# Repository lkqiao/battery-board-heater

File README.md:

# battery-board-heater
Subproject as part of the Stanford Student Space Initiative (SSI). This project provides the heater circuit used for the battery board of SAMWISE, the 2U CubeSat we are currently working on, to maintain optimal temperature for efficient auxiliary power supply to deployable structures, ADCS, radio, and a 12MP camera + selfie stick. 

The schematic of the heater circuit is provided in KiCAD and is integrated into the main battery board PCB and external systems of the satellite. The coordinates of the heating coil traces are automatically generated via Python script.

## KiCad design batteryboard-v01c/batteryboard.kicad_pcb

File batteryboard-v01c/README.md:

# PyCubed Battery Board

2S3P Li-ion battery pack for CubeSat designs.
   - Fits 18650 cells (like the LG INR18650-MJ1)
   - Meets maximum capacity requirements of common CubeSat integrators
   - Uses components with radiation testing heritage
      - R5460x2xx for protection against
         - over-charge 
         - over-discharge
         - short-circuit
         - excess discharge-current
         - excess charge-current

## Interactive Bill of Materials 🛒
- [batteryboard-v01](https://pycubed.github.io/hardware/batteryboard-v01)

<br>
<br>
<br>
<br />This work is licensed under a <a rel="license" href="http://creativecommons.org/licenses/by/4.0/">Creative Commons Attribution 4.0 International License</a>.

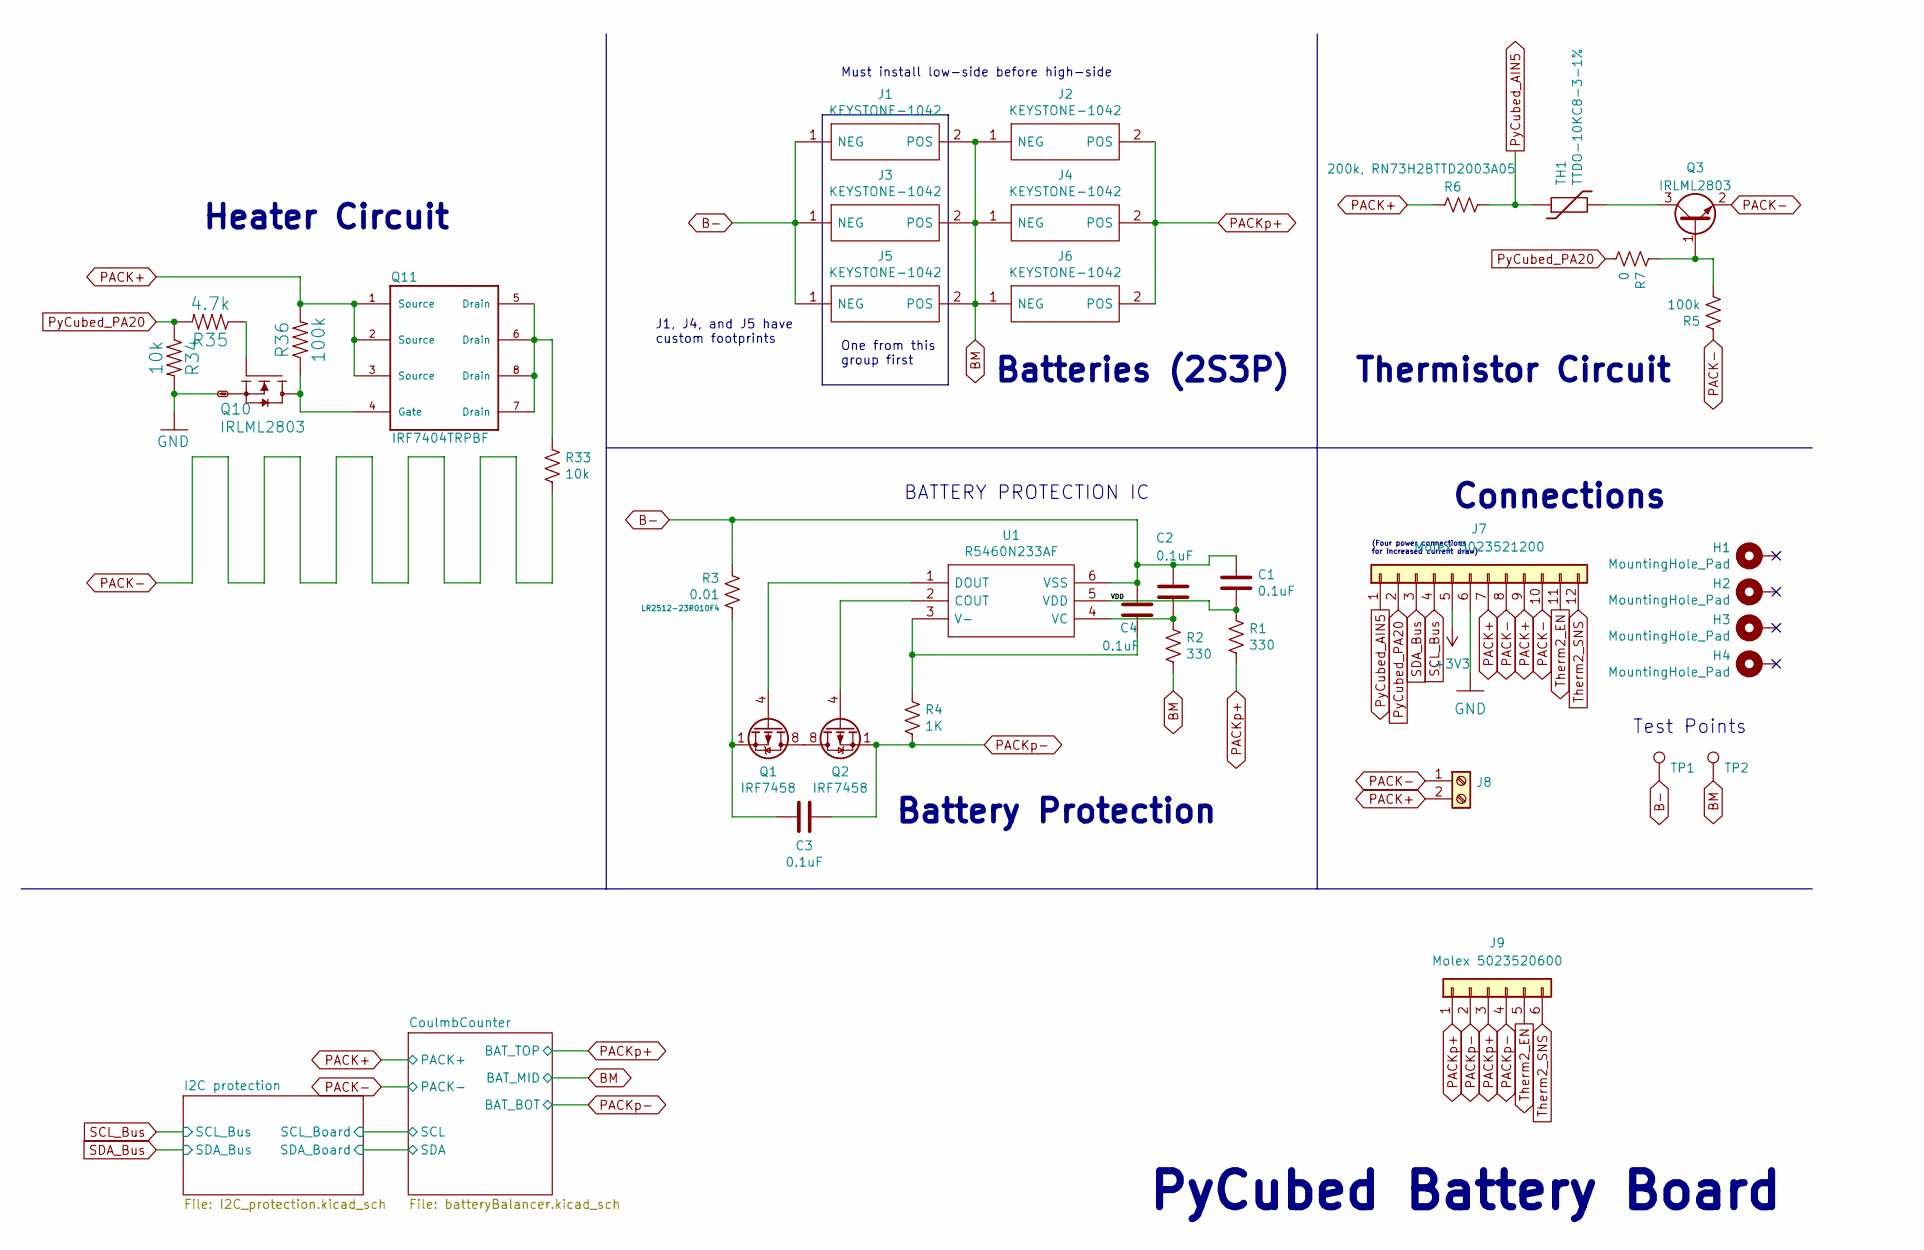
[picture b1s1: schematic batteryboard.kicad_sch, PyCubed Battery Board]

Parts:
C1, C2, C3, C4: 0.1uF; C_0603_1608Metric
H1, H2, H3, H4: MountingHole_Pad; MountingHole_3.2mm_M3_DIN965_PadMOD
J1: KEYSTONE-1042; Keystone_1042_J1; Manufacturer_Part_Number 1042; Mouser Part Number 534-1042
J2, J3, J6: KEYSTONE-1042; Keystone_1042; Manufacturer_Part_Number 1042; Mouser Part Number 534-1042
J4: KEYSTONE-1042; Keystone_1042_J4; Manufacturer_Part_Number 1042; Mouser Part Number 534-1042
J5: KEYSTONE-1042; Keystone_1042_J5; Manufacturer_Part_Number 1042; Mouser Part Number 534-1042
J7: Molex 5023521200; 5023521200
J8: Screw_Terminal_01x02; pheonix_2pos_screwterminal
J9: Molex 5023520600; 5023520600
Q1, Q2: IRF7458; SOIC-8_3.9x4.9mm_P1.27mm
Q3: IRLML2803; SOT-23
Q10: IRLML2803; SOT-23; Manufacturer_Part_Number MMBT2222AT
Q11: IRF7404TRPBF; Manufacturer_Part_Number NDS8434
R1, R2: 330; R_0603_1608Metric
R3: 0.01; R_2512_6332Metric
R4: 1K; R_0603_1608Metric; Manufacturer_Part_Number LR2512-23R010F4
R5, R36: 100k; R_0603_1608Metric
R6: 200k, RN73H2BTTD2003A05; R_1206_3216Metric
R7: 0; R_0603_1608Metric
R33, R34: 10k; R_0603_1608Metric
R35: 4.7k; R_0603_1608Metric
TH1: TTDO-10KC8-3-1%; R_Axial_DIN0204_L3.6mm_D1.6mm_P5.08mm_Horizontal
TP1, TP2: TestPoint; TestPoint_Loop_D1.80mm_Drill1.0mm_Beaded
U1: R5460N233AF; SOT-23-6; Manufacturer_Part_Number R5460N233AF-TR-FE; Mouser Part Number 848-R5460N233AFTRFE

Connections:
+3V3: J7.5; also elsewhere on the board
/VDD: C1.2, R1.2, U1.5 (VDD)
B-: C1.1, C2.1, C4.1, J1.1 (NEG), J3.1 (NEG), J5.1 (NEG), R3.1, TP1.1, U1.6 (VSS)
BM: J1.2 (POS), J2.1 (NEG), J3.2 (POS), J4.1 (NEG), J5.2 (POS), J6.1 (NEG), R2.1, TP2.1; also elsewhere on the board
GND: J7.6, Q10.2 (S), R34.2; also elsewhere on the board
unnamed: C3.1, Q1.1 (S), Q1.2 (S), Q1.3 (S), R3.2
unnamed: Q1.5 (D), Q1.6 (D), Q1.7 (D), Q1.8 (D), Q2.5 (D), Q2.6 (D), Q2.7 (D), Q2.8 (D)
unnamed: Q1.4 (G), U1.1 (DOUT)
unnamed: Q2.4 (G), U1.2 (COUT)
unnamed: Q3.1 (B), R5.1, R7.2
unnamed: Q3.3 (C), TH1.2
unnamed: Q10.3 (D), Q11.4 (Gate), R36.1
unnamed: Q10.1 (G), R35.1
unnamed: Q11.5 (Drain), Q11.6 (Drain), Q11.7 (Drain), Q11.8 (Drain), R33.2
unnamed: C4.2, R4.1, U1.3 (V-)
unnamed: C2.2, R2.2, U1.4 (VC)
PACK+: J7.7, J7.9, J8.2, Q11.1 (Source), Q11.2 (Source), Q11.3 (Source), R6.1, R36.2; also elsewhere on the board
PACK-: J7.8, J7.10, J8.1, Q3.2 (E), R5.2, R33.1; also elsewhere on the board
PACKp+: J2.2 (POS), J4.2 (POS), J6.2 (POS), J9.1, J9.3, R1.1; also elsewhere on the board
PACKp-: C3.2, J9.2, J9.4, Q2.1 (S), Q2.2 (S), Q2.3 (S), R4.2; also elsewhere on the board
PyCubed_AIN5: J7.1, R6.2, TH1.1
PyCubed_PA20: J7.2, R7.1, R34.1, R35.2
SCL_Bus: J7.4; also elsewhere on the board
SDA_Bus: J7.3; also elsewhere on the board
Therm2_EN: J7.11, J9.5
Therm2_SNS: J7.12, J9.6

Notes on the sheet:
Connections
(Four power connections for increased current draw)
One from this group first
PyCubed Battery Board
Batteries (2S3P)
Heater Circuit
Test Points
J1, J4, and J5 have custom footprints
Battery Protection
Must install low-side before high-side
Thermistor Circuit
BATTERY PROTECTION IC

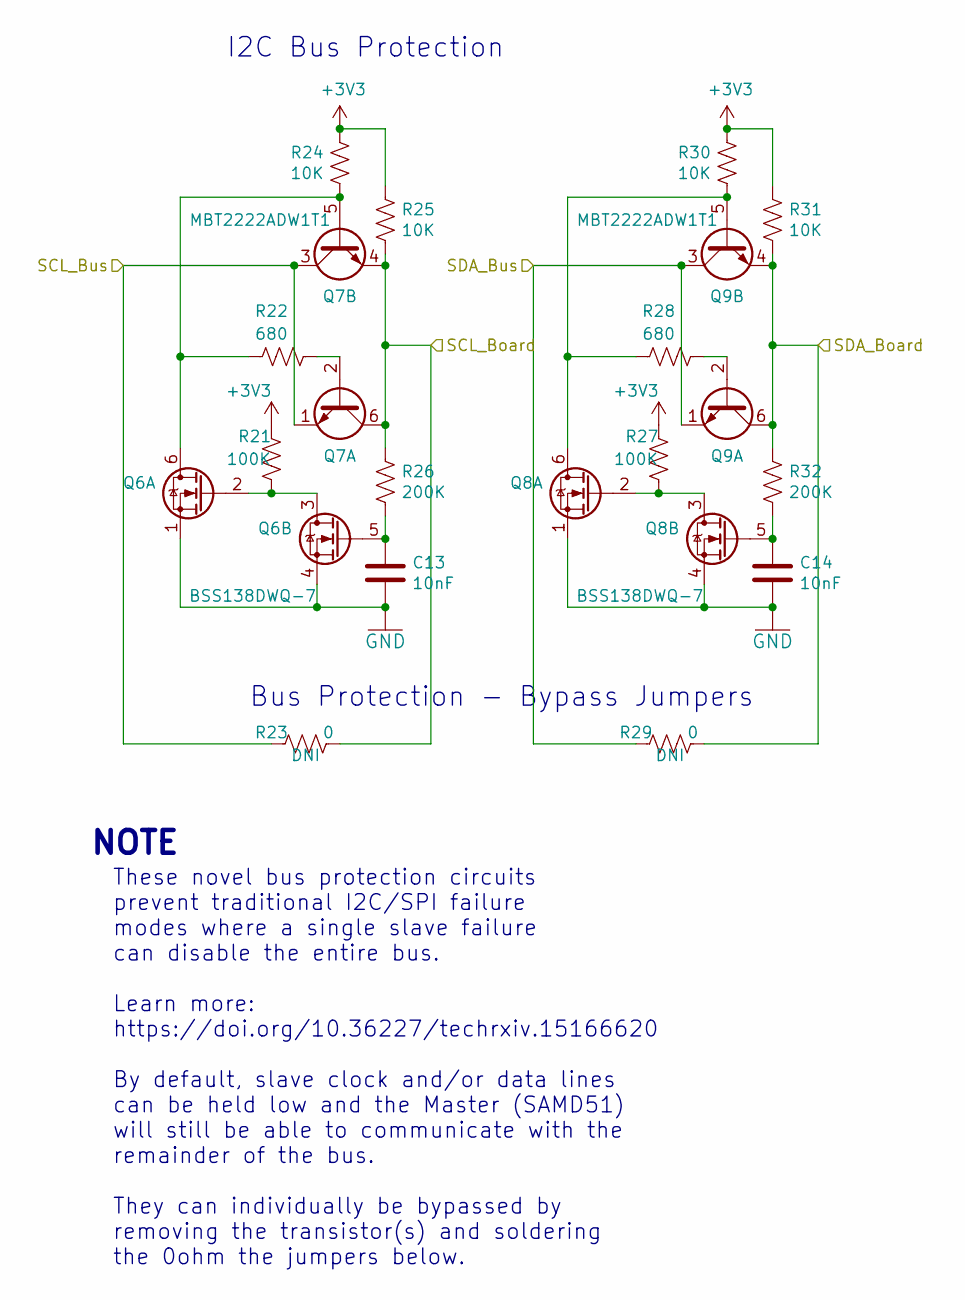
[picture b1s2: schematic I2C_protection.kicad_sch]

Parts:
C13, C14: 10nF; C_0603_1608Metric
Q6, Q8: BSS138DWQ-7; Manufacturer_Part_Number BSS138DWQ-7; Mouser Part Number 621-BSS138DWQ-7
Q7, Q9: MBT2222ADW1T1; SOT-363_SC-70-6; Manufacturer_Part_Number MBT2222ADW1T1G
R21, R27: 100K; R_0603_1608Metric
R22, R28: 680; R_0603_1608Metric
R23, R29: 0; R_0603_1608Metric
R24, R25, R30, R31: 10K; R_0603_1608Metric
R26, R32: 200K; R_0603_1608Metric

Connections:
+3V3: R21.1, R24.1, R25.1, R27.1, R30.1, R31.1; also elsewhere on the board
/CoulmbCounter/SCL: Q7.4 (E2), Q7.6 (C1), R23.1, R25.2, R26.1; also elsewhere on the board
/CoulmbCounter/SDA: Q9.4 (E2), Q9.6 (C1), R29.1, R31.2, R32.1; also elsewhere on the board
GND: C13.2, C14.2, Q6.1 (S2), Q6.4 (S1), Q8.1 (S2), Q8.4 (S1); also elsewhere on the board
unnamed: Q6.6 (D1), Q7.5 (B2), R22.2, R24.2
unnamed: Q6.2 (G2), Q6.3 (D2), R21.2
unnamed: C13.1, Q6.5 (G1), R26.2
unnamed: Q7.2 (B1), R22.1
unnamed: Q8.6 (D1), Q9.5 (B2), R28.2, R30.2
unnamed: Q8.2 (G2), Q8.3 (D2), R27.2
unnamed: C14.1, Q8.5 (G1), R32.2
unnamed: Q9.2 (B1), R28.1
SCL_Bus: Q7.1 (E1), Q7.3 (C2), R23.2; also elsewhere on the board
SDA_Bus: Q9.1 (E1), Q9.3 (C2), R29.2; also elsewhere on the board

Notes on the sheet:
NOTE
These novel bus protection circuits prevent traditional I2C/SPI failure modes where a single slave failure can disable the entire bus. Learn more: https://doi.org/10.36227/techrxiv.15166620 By default, slave clock and/or data lines can be held low and the Master (SAMD51) will still be able to commu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
Bus Protection - Bypass Jumpers
I2C Bus Protection

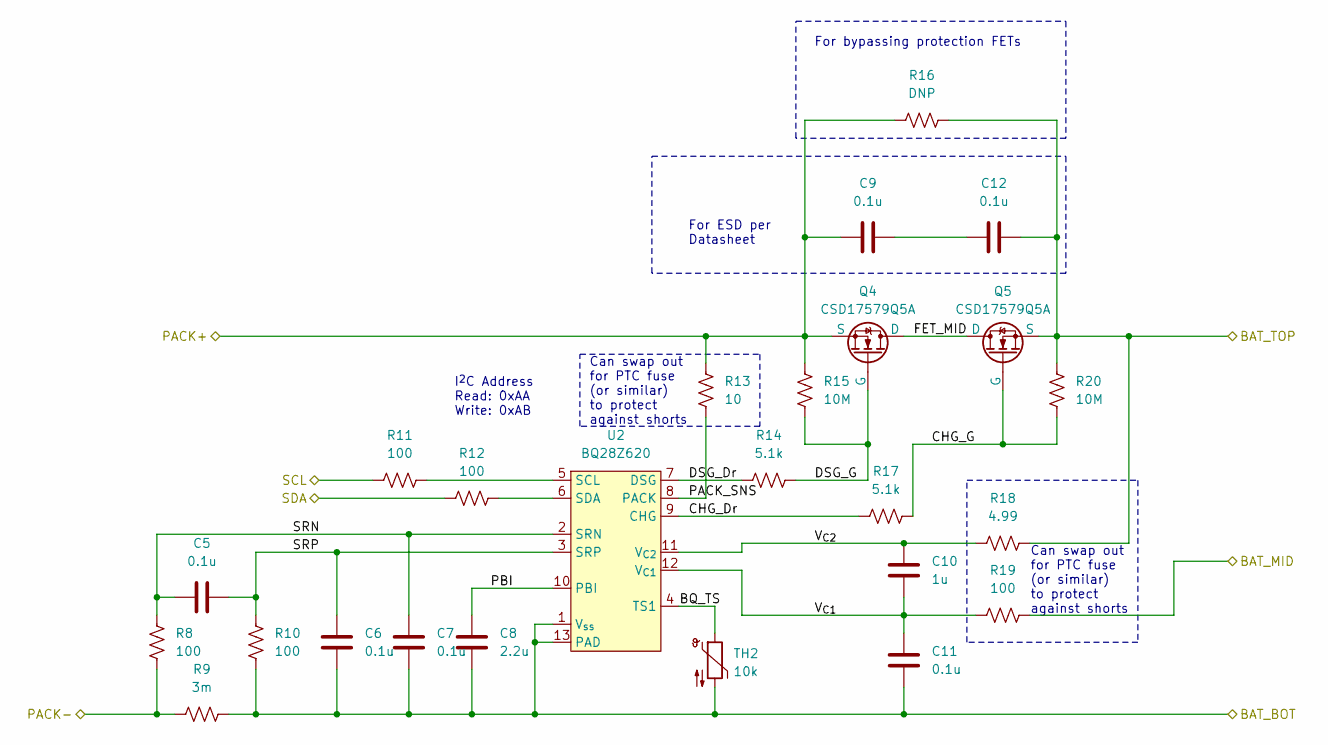
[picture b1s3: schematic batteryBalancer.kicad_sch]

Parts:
C5, C6, C7, C9, C11, C12: 0.1u; C_0603_1608Metric
C8: 2.2u; C_0603_1608Metric
C10: 1u; C_0603_1608Metric
Q4, Q5: CSD17579Q5A; DQJ8_NMOS_DGS
R8, R10, R11, R12, R19: 100; R_0603_1608Metric
R9: 3m; R_1206_3216Metric
R13: 10; R_0603_1608Metric
R14, R17: 5.1k; R_0603_1608Metric
R15, R20: 10M; R_0603_1608Metric
R16: DNP; R_1206_3216Metric
R18: 4.99; R_0603_1608Metric
TH2: 10k; R_Axial_DIN0204_L3.6mm_D1.6mm_P5.08mm_Horizontal
U2: BQ28Z620; VSON12_DRZ_TEX

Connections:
/CoulmbCounter/BQ_TS: TH2.1, U2.4 (TS1)
/CoulmbCounter/CHG_Dr: R17.1, U2.9 (CHG)
/CoulmbCounter/CHG_G: Q5.2 (G), R17.2, R20.2
/CoulmbCounter/DSG_Dr: R14.1, U2.7 (DSG)
/CoulmbCounter/DSG_G: Q4.2 (G), R14.2, R15.2
/CoulmbCounter/FET_MID: Q4.1 (D), Q5.1 (D)
/CoulmbCounter/PACK_SNS: R13.2, U2.8 (PACK)
/CoulmbCounter/PBI: C8.1, U2.10 (PBI)
/CoulmbCounter/SCL: R11.1; also elsewhere on the board
/CoulmbCounter/SDA: R12.1; also elsewhere on the board
/CoulmbCounter/SRN: C5.1, C7.1, R8.1, U2.2 (SRN)
/CoulmbCounter/SRP: C5.2, C6.1, R10.1, U2.3 (SRP)
/CoulmbCounter/V_{C1}: C10.2, C11.1, R19.1, U2.12 (V_{C1})
/CoulmbCounter/V_{C2}: C10.1, R18.1, U2.11 (V_{C2})
BM: R19.2; also elsewhere on the board
unnamed: C9.2, C12.1
unnamed: R11.2, U2.5 (SCL)
unnamed: R12.2, U2.6 (SDA)
PACK+: C9.1, Q4.3 (S), R13.1, R15.1, R16.1; also elsewhere on the board
PACK-: R8.2, R9.1; also elsewhere on the board
PACKp+: C12.2, Q5.3 (S), R16.2, R18.2, R20.1; also elsewhere on the board
PACKp-: C6.2, C7.2, C8.2, C11.2, R9.2, R10.2, TH2.2, U2.1 (V_{ss}), U2.13 (PAD); also elsewhere on the board

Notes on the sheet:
Can swap out for PTC fuse (or similar) to protect against shorts
For bypassing protection FETs
I^{2}C Address Read: 0xAA Write: 0xAB
For ESD per Datasheet

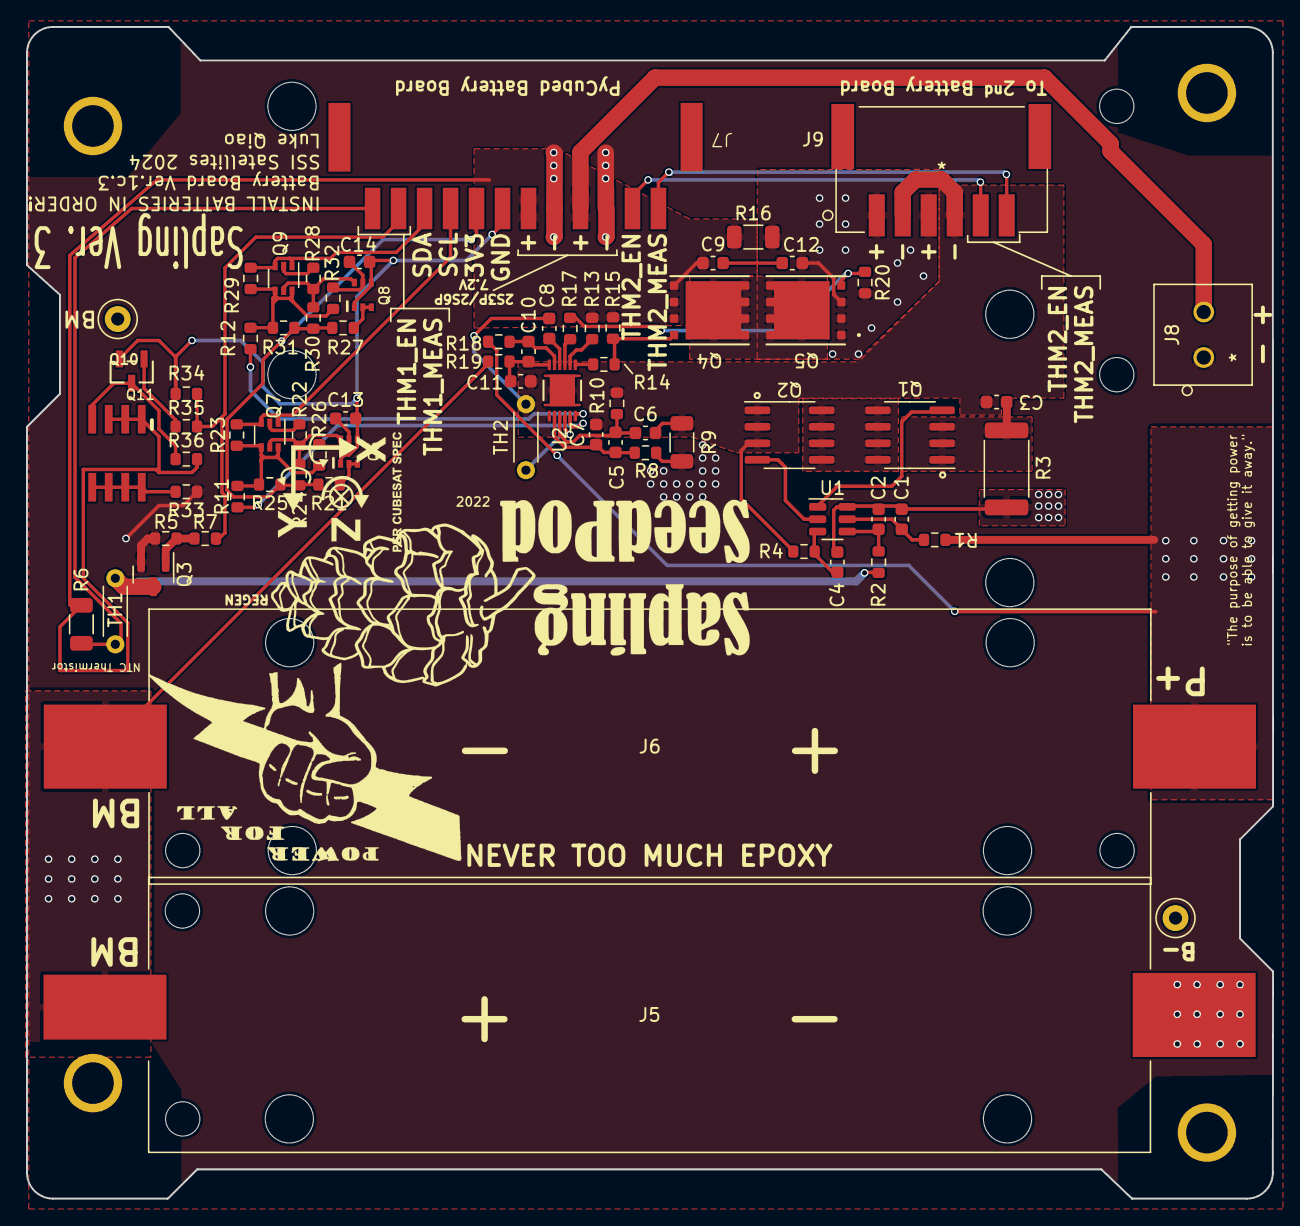
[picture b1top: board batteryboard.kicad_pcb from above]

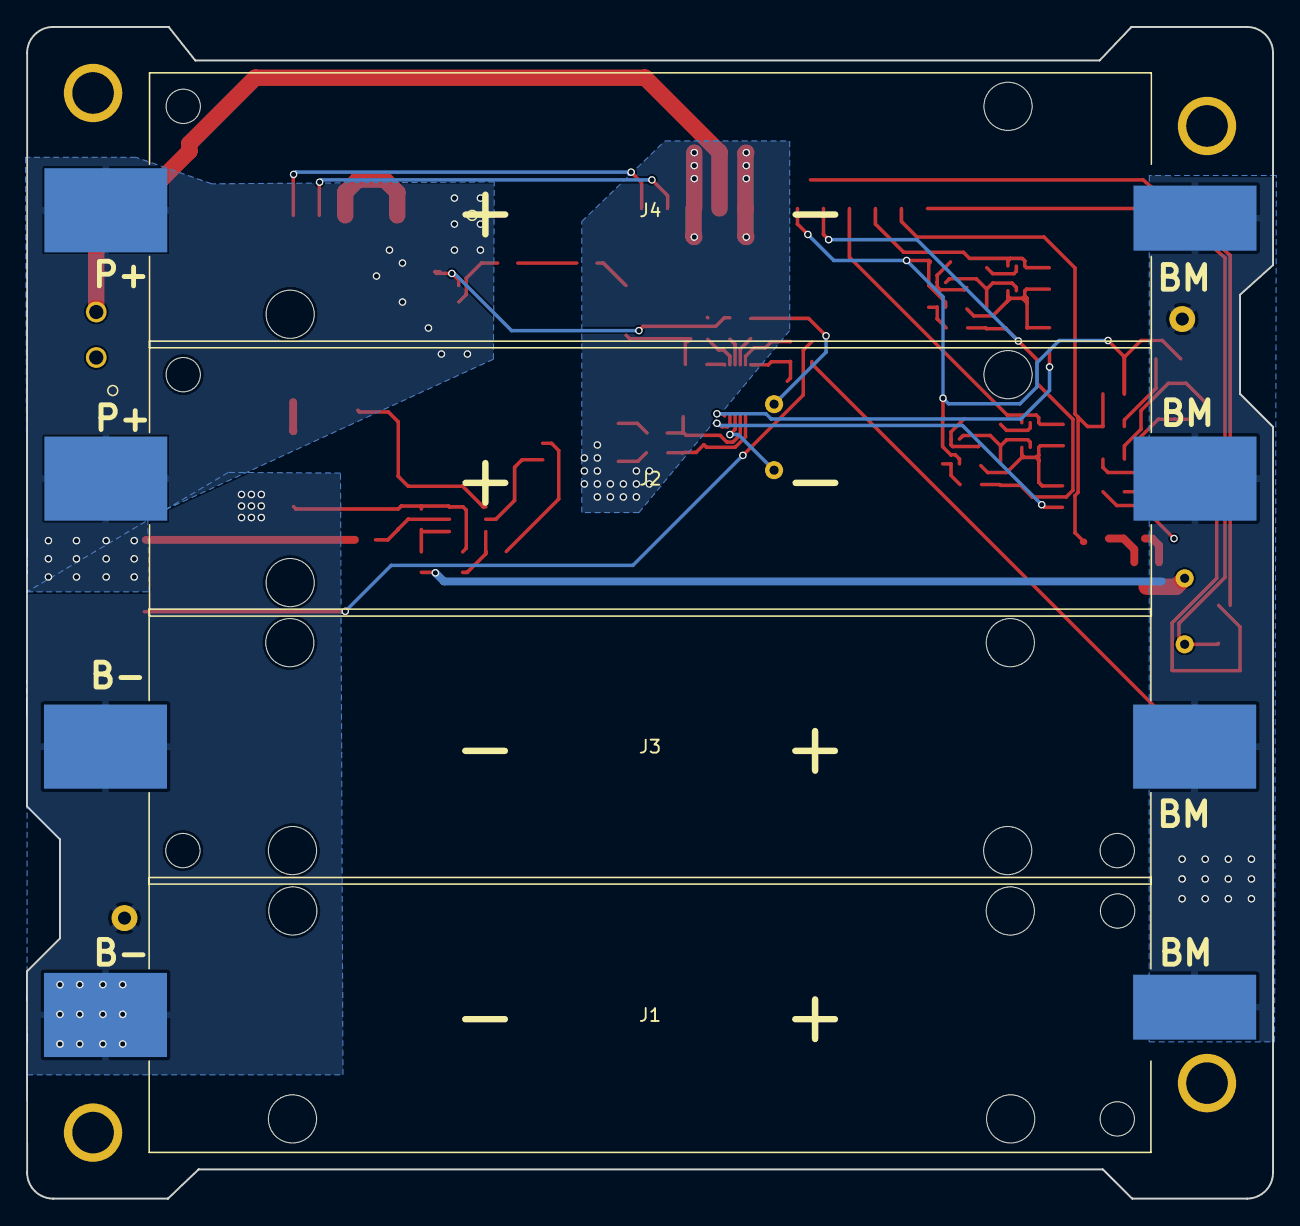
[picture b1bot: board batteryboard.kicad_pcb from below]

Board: 4 copper layers, 95.9 x 90.2 mm, 83 parts (5 on the bottom side), 51 nets.

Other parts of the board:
Ref**: Val**; PowerLogo
Ref**#2: Val**; SeedPodLogo
Ref**#3: Val**; XYZ_cubesat-bot

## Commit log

2023-12-08 Optimized coil shape
2025-09-10 updated silkscreen
2025-09-10 cleaned up
2025-09-10 restructuring
2025-09-10 restructure project

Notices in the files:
parts and their libraries:
Copyright 2021 Accelerated Designs. All rights reserved.
